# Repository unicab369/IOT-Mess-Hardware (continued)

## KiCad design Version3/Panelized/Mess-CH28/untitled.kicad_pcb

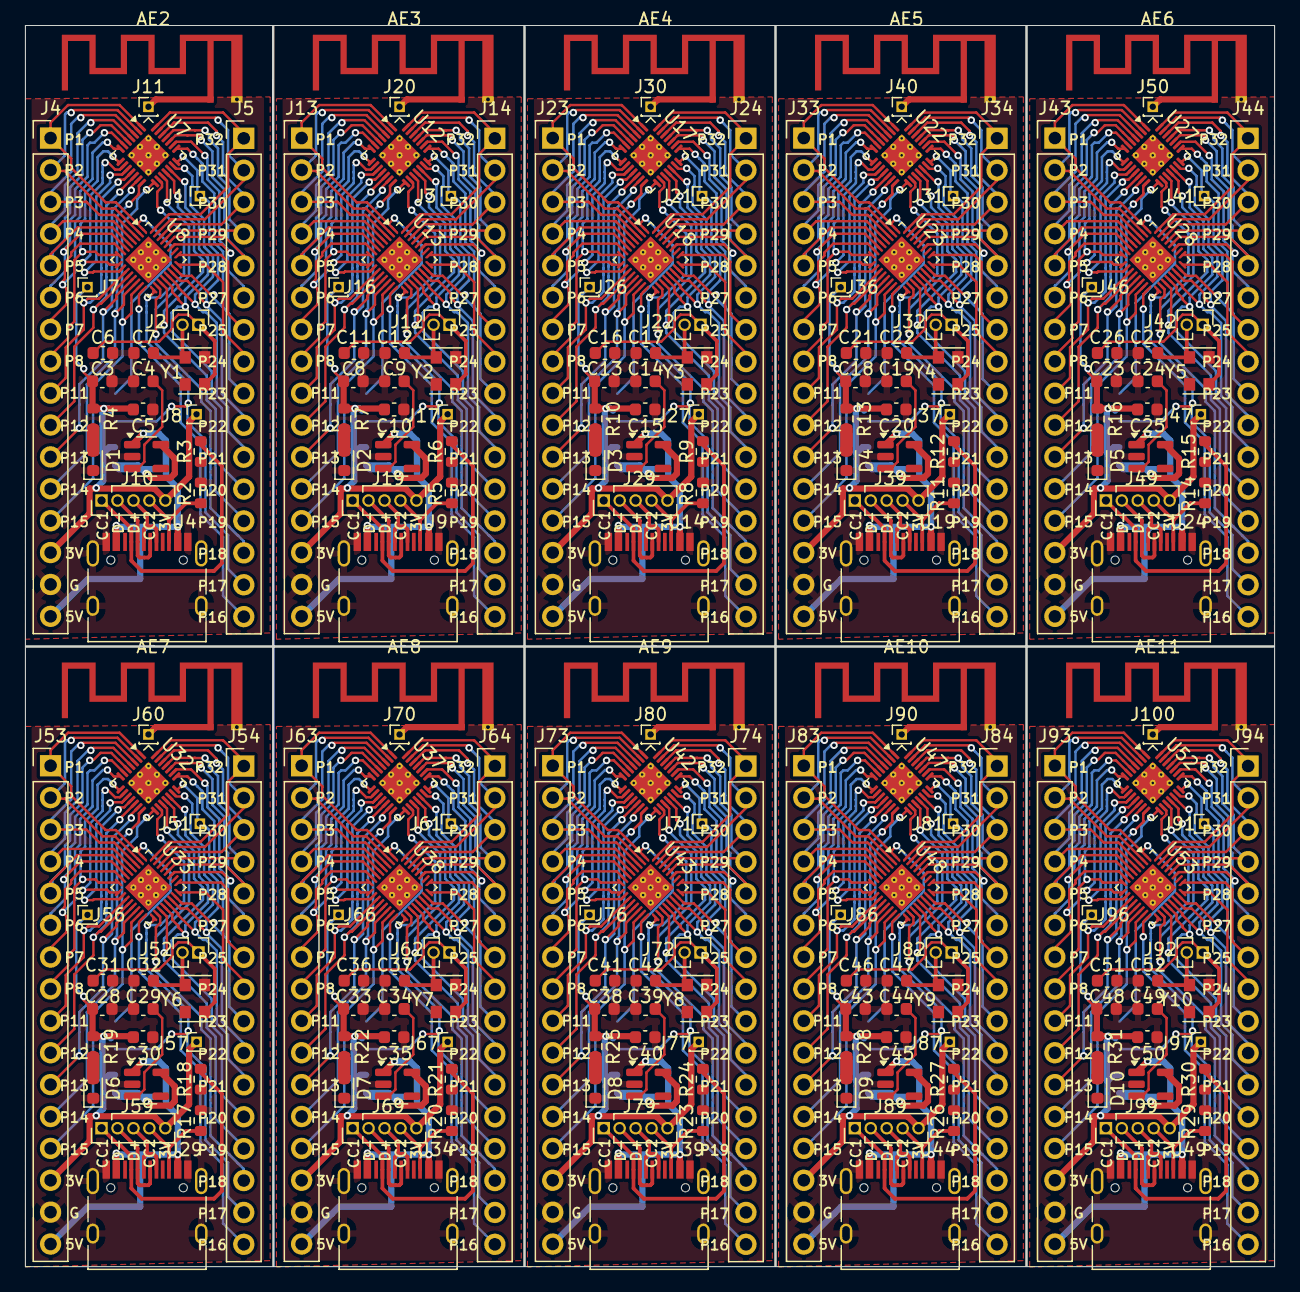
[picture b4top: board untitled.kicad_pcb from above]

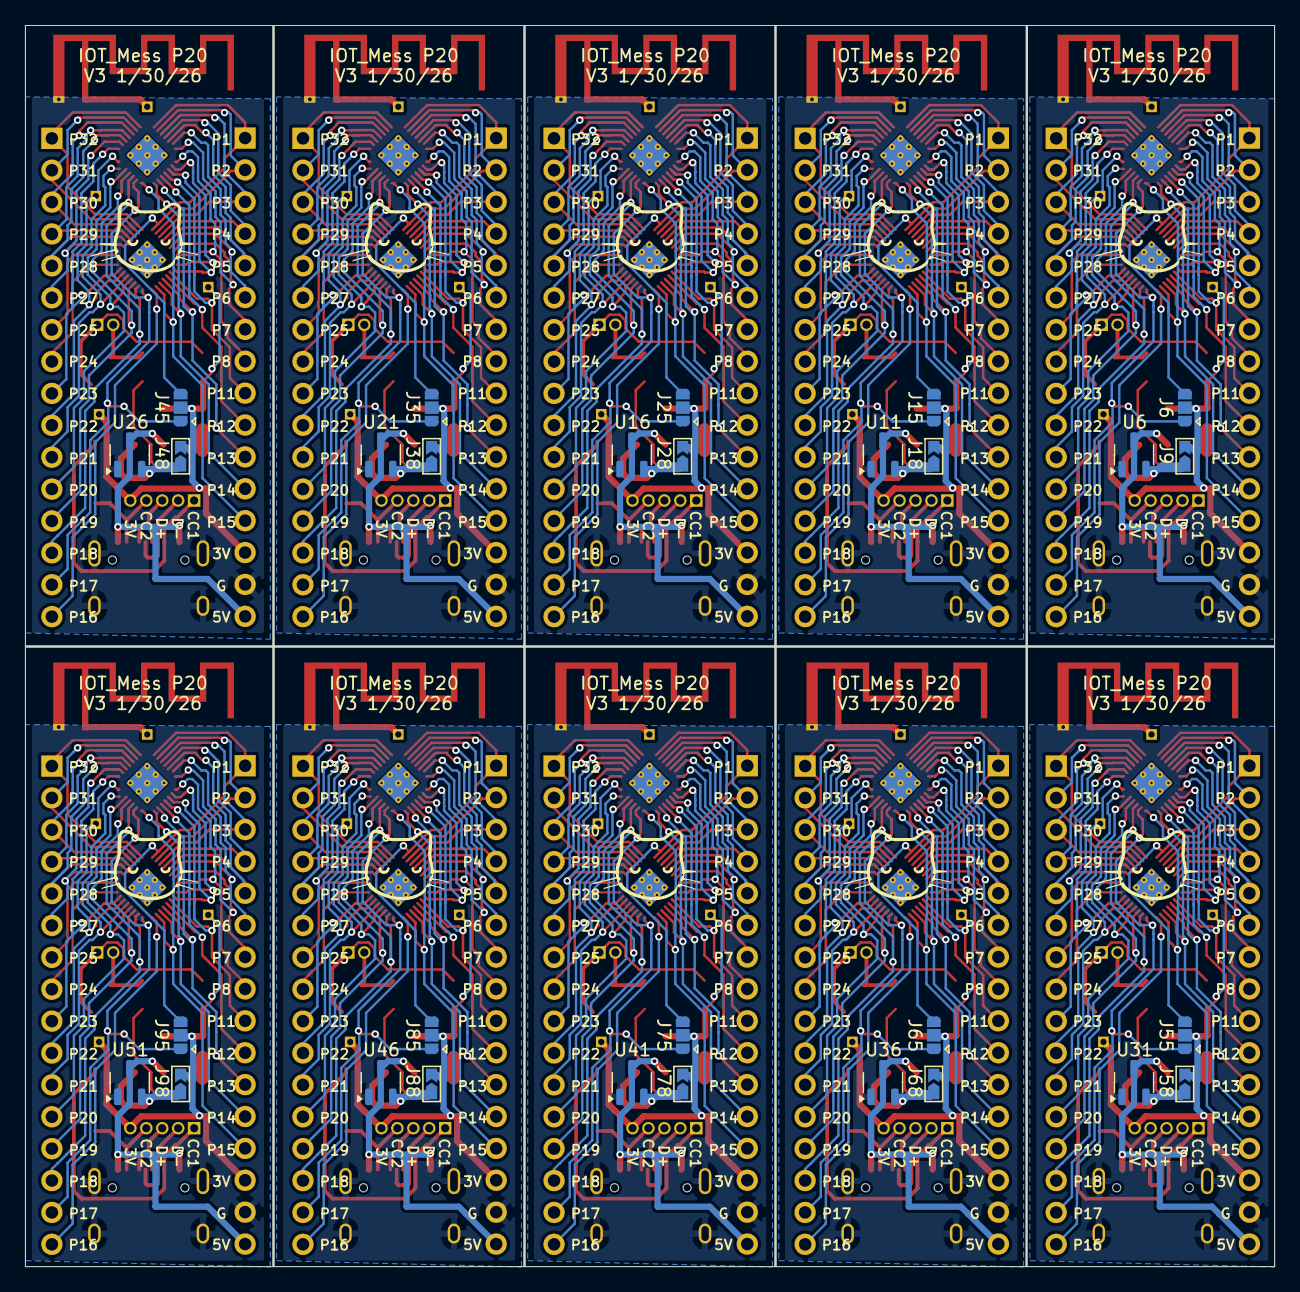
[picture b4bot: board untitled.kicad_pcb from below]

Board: 2 copper layers, 99.5 x 98.9 mm, 260 parts (30 on the bottom side), 45 nets.

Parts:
AE2, AE3, AE4, AE5, AE6, AE7, AE8, AE9, AE10, AE11: Antenna_Shield; Texas_SWRA117D_2.4GHz_Left
C3, C8, C13, C18, C23, C28, C33, C38, C43, C48: 10u; C_0603_1608Metric
C4, C5, C9, C10, C14, C15, C19, C20, C24, C25, C29, C30, C34, C35, C39, C40, C44, C45, C49, C50: 1u; C_0603_1608Metric
C6, C7, C11, C12, C16, C17, C21, C22, C26, C27, C31, C32, C36, C37, C41, C42, C46, C47, C51, C52: 12-25pF; C_0603_1608Metric
D1, D2, D3, D4, D5, D6, D7, D8, D9, D10: LED; LED_0603_1608Metric
J1, J3, J7, J8, J11, J16, J17, J20, J21, J26, J27, J30, J31, J36, J37, J40, J41, J46, J47, J50, J51, J56, J57, J60, J61, J66, J67, J70, J71, J76, J77, J80, J81, J86, J87, J90, J91, J96, J97, J100: Conn_01x01_Pin; PinHeader_1x01_P1.00mm_Vertical
J2, J12, J22, J32, J42, J52, J62, J72, J82, J92: Conn_01x02_Pin; PinHeader_1x02_P1.27mm_Vertical
J4, J5, J13, J14, J23, J24, J33, J34, J43, J44, J53, J54, J63, J64, J73, J74, J83, J84, J93, J94: Conn_01x16_Pin; PinHeader_1x16_P2.54mm_Vertical
J6, J15, J25, J35, J45, J55, J65, J75, J85, J95: Jumper; Jumper-3_P1.3mm_Open_RoundedPad1.0x1.5mm
J9, J18, J28, J38, J48, J58, J68, J78, J88, J98: Jumper_2; Jumpper-triangle
J10, J19, J29, J39, J49, J59, J69, J79, J89, J99: Conn_01x05_Pin; PinHeader_1x05_P1.27mm_Vertical
R2, R3, R5, R6, R8, R9, R11, R12, R14, R15, R17, R18, R20, R21, R23, R24, R26, R27, R29, R30: 5.1K; R_0603_1608Metric
R4, R7, R10, R13, R16, R19, R22, R25, R28, R31: R; R_0603_1608Metric
U4, U9, U14, U19, U24, U29, U34, U39, U44, U49: USB_C_Receptacle_USB2.0_16P; USB_C_Receptacle_HRO_TYPE-C-31-M-12
U5, U10, U15, U20, U25, U30, U35, U40, U45, U50: ME6211C33M5; SOT-23-5
U6, U11, U16, U21, U26, U31, U36, U41, U46, U51: XC6206PxxxMR; SOT-23-3
U7, U12, U17, U22, U27, U32, U37, U42, U47, U52: QFN-28-1EP_4x4mm_P0.4mm_EP2.4x2.4mm_ThermalVias
U8, U13, U18, U23, U28, U33, U38, U43, U48, U53: QFN-32-1EP_4x4mm_P0.4mm_EP2.65x2.65mm_ThermalVias
Y1, Y2, Y3, Y4, Y5, Y6, Y7, Y8, Y9, Y10: XO32; Oscillator_SMD_EuroQuartz_XO32-4Pin_3.2x2.5mm

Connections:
5V: J4.16, J13.16, J23.16, J33.16, J43.16, J53.16, J63.16, J73.16, J83.16, J93.16, U4.A4 (VBUS), U4.A9 (VBUS), U4.B4 (VBUS), U4.B9 (VBUS), U5.1 (V_{IN}), U6.3 (VI), U9.A4 (VBUS), U9.A9 (VBUS), U9.B4 (VBUS), U9.B9 (VBUS), U10.1 (V_{IN}), U11.3 (VI), U14.A4 (VBUS), U14.A9 (VBUS), U14.B4 (VBUS), U14.B9 (VBUS), U15.1 (V_{IN}), U16.3 (VI), U19.A4 (VBUS), U19.A9 (VBUS), U19.B4 (VBUS), U19.B9 (VBUS), U20.1 (V_{IN}), U21.3 (VI), U24.A4 (VBUS), U24.A9 (VBUS), U24.B4 (VBUS), U24.B9 (VBUS), U25.1 (V_{IN}), U26.3 (VI), U29.A4 (VBUS), U29.A9 (VBUS), U29.B4 (VBUS), U29.B9 (VBUS), U30.1 (V_{IN}), U31.3 (VI), U34.A4 (VBUS), U34.A9 (VBUS), U34.B4 (VBUS), U34.B9 (VBUS), U35.1 (V_{IN}), U36.3 (VI), U39.A4 (VBUS), U39.A9 (VBUS), U39.B4 (VBUS), U39.B9 (VBUS), U40.1 (V_{IN}), U41.3 (VI), U44.A4 (VBUS), U44.A9 (VBUS), U44.B4 (VBUS), U44.B9 (VBUS), U45.1 (V_{IN}), U46.3 (VI), U49.A4 (VBUS), U49.A9 (VBUS), U49.B4 (VBUS), U49.B9 (VBUS), U50.1 (V_{IN}), U51.3 (VI)
+3.3V: C3.1, C5.1, C8.1, C10.1, C13.1, C15.1, C18.1, C20.1, C23.1, C25.1, C28.1, C30.1, C33.1, C35.1, C38.1, C40.1, C43.1, C45.1, C48.1, C50.1, J4.14, J6.2 (C), J7.1, J8.1, J9.2 (B), J10.5, J13.14, J15.2 (C), J16.1, J17.1, J18.2 (B), J19.5, J23.14, J25.2 (C), J26.1, J27.1, J28.2 (B), J29.5, J33.14, J35.2 (C), J36.1, J37.1, J38.2 (B), J39.5, J43.14, J45.2 (C), J46.1, J47.1, J48.2 (B), J49.5, J53.14, J55.2 (C), J56.1, J57.1, J58.2 (B), J59.5, J63.14, J65.2 (C), J66.1, J67.1, J68.2 (B), J69.5, J73.14, J75.2 (C), J76.1, J77.1, J78.2 (B), J79.5, J83.14, J85.2 (C), J86.1, J87.1, J88.2 (B), J89.5, J93.14, J95.2 (C), J96.1, J97.1, J98.2 (B), J99.5, R4.1, R7.1, R10.1, R13.1, R16.1, R19.1, R22.1, R25.1, R28.1, R31.1
ANT: AE2.1 (A), AE3.1 (A), AE4.1 (A), AE5.1 (A), AE6.1 (A), AE7.1 (A), AE8.1 (A), AE9.1 (A), AE10.1 (A), AE11.1 (A), J11.1, J20.1, J30.1, J40.1, J50.1, J60.1, J70.1, J80.1, J90.1, J100.1
CC1: J10.1, J19.1, J29.1, J39.1, J49.1, J59.1, J69.1, J79.1, J89.1, J99.1, R3.1, R6.1, R9.1, R12.1, R15.1, R18.1, R21.1, R24.1, R27.1, R30.1, U4.A5 (CC1), U9.A5 (CC1), U14.A5 (CC1), U19.A5 (CC1), U24.A5 (CC1), U29.A5 (CC1), U34.A5 (CC1), U39.A5 (CC1), U44.A5 (CC1), U49.A5 (CC1)
CC2: J10.4, J19.4, J29.4, J39.4, J49.4, J59.4, J69.4, J79.4, J89.4, J99.4, R2.1, R5.1, R8.1, R11.1, R14.1, R17.1, R20.1, R23.1, R26.1, R29.1, U4.B5 (CC2), U9.B5 (CC2), U14.B5 (CC2), U19.B5 (CC2), U24.B5 (CC2), U29.B5 (CC2), U34.B5 (CC2), U39.B5 (CC2), U44.B5 (CC2), U49.B5 (CC2)
D+: J10.3, J19.3, J29.3, J39.3, J49.3, J59.3, J69.3, J79.3, J89.3, J99.3, U4.A6 (D+), U4.B6 (D+), U9.A6 (D+), U9.B6 (D+), U14.A6 (D+), U14.B6 (D+), U19.A6 (D+), U19.B6 (D+), U24.A6 (D+), U24.B6 (D+), U29.A6 (D+), U29.B6 (D+), U34.A6 (D+), U34.B6 (D+), U39.A6 (D+), U39.B6 (D+), U44.A6 (D+), U44.B6 (D+), U49.A6 (D+), U49.B6 (D+)
D-: J10.2, J19.2, J29.2, J39.2, J49.2, J59.2, J69.2, J79.2, J89.2, J99.2, U4.A7 (D-), U4.B7 (D-), U9.A7 (D-), U9.B7 (D-), U14.A7 (D-), U14.B7 (D-), U19.A7 (D-), U19.B7 (D-), U24.A7 (D-), U24.B7 (D-), U29.A7 (D-), U29.B7 (D-), U34.A7 (D-), U34.B7 (D-), U39.A7 (D-), U39.B7 (D-), U44.A7 (D-), U44.B7 (D-), U49.A7 (D-), U49.B7 (D-)
GND: AE2.2 (Shield), AE3.2 (Shield), AE4.2 (Shield), AE5.2 (Shield), AE6.2 (Shield), AE7.2 (Shield), AE8.2 (Shield), AE9.2 (Shield), AE10.2 (Shield), AE11.2 (Shield), C3.2, C4.2, C5.2, C6.2, C7.2, C8.2, C9.2, C10.2, C11.2, C12.2, C13.2, C14.2, C15.2, C16.2, C17.2, C18.2, C19.2, C20.2, C21.2, C22.2, C23.2, C24.2, C25.2, C26.2, C27.2, C28.2, C29.2, C30.2, C31.2, C32.2, C33.2, C34.2, C35.2, C36.2, C37.2, C38.2, C39.2, C40.2, C41.2, C42.2, C43.2, C44.2, C45.2, C46.2, C47.2, C48.2, C49.2, C50.2, C51.2, C52.2, D1.1 (K), D2.1 (K), D3.1 (K), D4.1 (K), D5.1 (K), D6.1 (K), D7.1 (K), D8.1 (K), D9.1 (K), D10.1 (K), J4.15, J13.15, J23.15, J33.15, J43.15, J53.15, J63.15, J73.15, J83.15, J93.15, R2.2, R3.2, R5.2, R6.2, R8.2, R9.2, R11.2, R12.2, R14.2, R15.2, R17.2, R18.2, R20.2, R21.2, R23.2, R24.2, R26.2, R27.2, R29.2, R30.2, U4.A1 (GND), U4.A12 (GND), U4.B1 (GND), U4.B12 (GND), U4.S1 (SHIELD), U5.2 (V_{SS}), U6.1 (GND), U9.A1 (GND), U9.A12 (GND), U9.B1 (GND), U9.B12 (GND), U9.S1 (SHIELD), U10.2 (V_{SS}), U11.1 (GND), U14.A1 (GND), U14.A12 (GND), U14.B1 (GND), U14.B12 (GND), U14.S1 (SHIELD), U15.2 (V_{SS}), U16.1 (GND), U19.A1 (GND), U19.A12 (GND), U19.B1 (GND), U19.B12 (GND), U19.S1 (SHIELD), U20.2 (V_{SS}), U21.1 (GND), U24.A1 (GND), U24.A12 (GND), U24.B1 (GND), U24.B12 (GND), U24.S1 (SHIELD), U25.2 (V_{SS}), U26.1 (GND), U29.A1 (GND), U29.A12 (GND), U29.B1 (GND), U29.B12 (GND), U29.S1 (SHIELD), U30.2 (V_{SS}), U31.1 (GND), U34.A1 (GND), U34.A12 (GND), U34.B1 (GND), U34.B12 (GND), U34.S1 (SHIELD), U35.2 (V_{SS}), U36.1 (GND), U39.A1 (GND), U39.A12 (GND), U39.B1 (GND), U39.B12 (GND), U39.S1 (SHIELD), U40.2 (V_{SS}), U41.1 (GND), U44.A1 (GND), U44.A12 (GND), U44.B1 (GND), U44.B12 (GND), U44.S1 (SHIELD), U45.2 (V_{SS}), U46.1 (GND), U49.A1 (GND), U49.A12 (GND), U49.B1 (GND), U49.B12 (GND), U49.S1 (SHIELD), U50.2 (V_{SS}), U51.1 (GND), Y1.2 (GND), Y1.4 (GND), Y2.2 (GND), Y2.4 (GND), Y3.2 (GND), Y3.4 (GND), Y4.2 (GND), Y4.4 (GND), Y5.2 (GND), Y5.4 (GND), Y6.2 (GND), Y6.4 (GND), Y7.2 (GND), Y7.4 (GND), Y8.2 (GND), Y8.4 (GND), Y9.2 (GND), Y9.4 (GND), Y10.2 (GND), Y10.4 (GND)
LDO_EN: C4.1, C9.1, C14.1, C19.1, C24.1, C29.1, C34.1, C39.1, C44.1, C49.1, U5.3 (CE), U10.3 (CE), U15.3 (CE), U20.3 (CE), U25.3 (CE), U30.3 (CE), U35.3 (CE), U40.3 (CE), U45.3 (CE), U50.3 (CE)
unnamed: D1.2 (A), D2.2 (A), D3.2 (A), D4.2 (A), D5.2 (A), D6.2 (A), D7.2 (A), D8.2 (A), D9.2 (A), D10.2 (A), R4.2, R7.2, R10.2, R13.2, R16.2, R19.2, R22.2, R25.2, R28.2, R31.2
unnamed: C6.1, C11.1, C16.1, C21.1, C26.1, C31.1, C36.1, C41.1, C46.1, C51.1, J2.1, J12.1, J22.1, J32.1, J42.1, J52.1, J62.1, J72.1, J82.1, J92.1, Y1.1 (XI), Y2.1 (XI), Y3.1 (XI), Y4.1 (XI), Y5.1 (XI), Y6.1 (XI), Y7.1 (XI), Y8.1 (XI), Y9.1 (XI), Y10.1 (XI)
unnamed: C7.1, C12.1, C17.1, C22.1, C27.1, C32.1, C37.1, C42.1, C47.1, C52.1, J2.2, J12.2, J22.2, J32.2, J42.2, J52.2, J62.2, J72.2, J82.2, J92.2, Y1.3 (XO), Y2.3 (XO), Y3.3 (XO), Y4.3 (XO), Y5.3 (XO), Y6.3 (XO), Y7.3 (XO), Y8.3 (XO), Y9.3 (XO), Y10.3 (XO)
unnamed: J9.1 (A), J18.1 (A), J28.1 (A), J38.1 (A), J48.1 (A), J58.1 (A), J68.1 (A), J78.1 (A), J88.1 (A), J98.1 (A), U5.5 (V_{OUT}), U6.2 (VO), U10.5 (V_{OUT}), U11.2 (VO), U15.5 (V_{OUT}), U16.2 (VO), U20.5 (V_{OUT}), U21.2 (VO), U25.5 (V_{OUT}), U26.2 (VO), U30.5 (V_{OUT}), U31.2 (VO), U35.5 (V_{OUT}), U36.2 (VO), U40.5 (V_{OUT}), U41.2 (VO), U45.5 (V_{OUT}), U46.2 (VO), U50.5 (V_{OUT}), U51.2 (VO)
P_1: J4.1, J6.3 (B), J13.1, J15.3 (B), J23.1, J25.3 (B), J33.1, J35.3 (B), J43.1, J45.3 (B), J53.1, J55.3 (B), J63.1, J65.3 (B), J73.1, J75.3 (B), J83.1, J85.3 (B), J93.1, J95.3 (B), U7.1 (PB8/BOOT), U8.1 (B3/SWCK-VDD), U12.1 (PB8/BOOT), U13.1 (B3/SWCK-VDD), U17.1 (PB8/BOOT), U18.1 (B3/SWCK-VDD), U22.1 (PB8/BOOT), U23.1 (B3/SWCK-VDD), U27.1 (PB8/BOOT), U28.1 (B3/SWCK-VDD), U32.1 (PB8/BOOT), U33.1 (B3/SWCK-VDD), U37.1 (PB8/BOOT), U38.1 (B3/SWCK-VDD), U42.1 (PB8/BOOT), U43.1 (B3/SWCK-VDD), U47.1 (PB8/BOOT), U48.1 (B3/SWCK-VDD), U52.1 (PB8/BOOT), U53.1 (B3/SWCK-VDD)
P_2: J4.2, J13.2, J23.2, J33.2, J43.2, J53.2, J63.2, J73.2, J83.2, J93.2, U7.2 (PD0/XI-VDD), U8.2 (PA5-VDCID), U12.2 (PD0/XI-VDD), U13.2 (PA5-VDCID), U17.2 (PD0/XI-VDD), U18.2 (PA5-VDCID), U22.2 (PD0/XI-VDD), U23.2 (PA5-VDCID), U27.2 (PD0/XI-VDD), U28.2 (PA5-VDCID), U32.2 (PD0/XI-VDD), U33.2 (PA5-VDCID), U37.2 (PD0/XI-VDD), U38.2 (PA5-VDCID), U42.2 (PD0/XI-VDD), U43.2 (PA5-VDCID), U47.2 (PD0/XI-VDD), U48.2 (PA5-VDCID), U52.2 (PD0/XI-VDD), U53.2 (PA5-VDCID)
P_3: J4.3, J13.3, J23.3, J33.3, J43.3, J53.3, J63.3, J73.3, J83.3, J93.3, U7.3 (PD1/X0), U8.3 (PA6-VSW), U12.3 (PD1/X0), U13.3 (PA6-VSW), U17.3 (PD1/X0), U18.3 (PA6-VSW), U22.3 (PD1/X0), U23.3 (PA6-VSW), U27.3 (PD1/X0), U28.3 (PA6-VSW), U32.3 (PD1/X0), U33.3 (PA6-VSW), U37.3 (PD1/X0), U38.3 (PA6-VSW), U42.3 (PD1/X0), U43.3 (PA6-VSW), U47.3 (PD1/X0), U48.3 (PA6-VSW), U52.3 (PD1/X0), U53.3 (PA6-VSW)
P_4: J4.4, J13.4, J23.4, J33.4, J43.4, J53.4, J63.4, J73.4, J83.4, J93.4, U7.4 (RST-VDDA), U8.4 (PA7/RST-XI-VDCID), U12.4 (RST-VDDA), U13.4 (PA7/RST-XI-VDCID), U17.4 (RST-VDDA), U18.4 (PA7/RST-XI-VDCID), U22.4 (RST-VDDA), U23.4 (PA7/RST-XI-VDCID), U27.4 (RST-VDDA), U28.4 (PA7/RST-XI-VDCID), U32.4 (RST-VDDA), U33.4 (PA7/RST-XI-VDCID), U37.4 (RST-VDDA), U38.4 (PA7/RST-XI-VDCID), U42.4 (RST-VDDA), U43.4 (PA7/RST-XI-VDCID), U47.4 (RST-VDDA), U48.4 (PA7/RST-XI-VDCID), U52.4 (RST-VDDA), U53.4 (PA7/RST-XI-VDCID)
P_5: J4.5, J13.5, J23.5, J33.5, J43.5, J53.5, J63.5, J73.5, J83.5, J93.5, U7.5 (VDDA), U8.5 (PA0-X0-VSW), U12.5 (VDDA), U13.5 (PA0-X0-VSW), U17.5 (VDDA), U18.5 (PA0-X0-VSW), U22.5 (VDDA), U23.5 (PA0-X0-VSW), U27.5 (VDDA), U28.5 (PA0-X0-VSW), U32.5 (VDDA), U33.5 (PA0-X0-VSW), U37.5 (VDDA), U38.5 (PA0-X0-VSW), U42.5 (VDDA), U43.5 (PA0-X0-VSW), U47.5 (VDDA), U48.5 (PA0-X0-VSW), U52.5 (VDDA), U53.5 (PA0-X0-VSW)
P_6: J4.6, J13.6, J23.6, J33.6, J43.6, J53.6, J63.6, J73.6, J83.6, J93.6, U7.6 (PA0/WKUP/A0), U8.6 (PA1/XI), U12.6 (PA0/WKUP/A0), U13.6 (PA1/XI), U17.6 (PA0/WKUP/A0), U18.6 (PA1/XI), U22.6 (PA0/WKUP/A0), U23.6 (PA1/XI), U27.6 (PA0/WKUP/A0), U28.6 (PA1/XI), U32.6 (PA0/WKUP/A0), U33.6 (PA1/XI), U37.6 (PA0/WKUP/A0), U38.6 (PA1/XI), U42.6 (PA0/WKUP/A0), U43.6 (PA1/XI), U47.6 (PA0/WKUP/A0), U48.6 (PA1/XI), U52.6 (PA0/WKUP/A0), U53.6 (PA1/XI)
P_7: J4.7, J13.7, J23.7, J33.7, J43.7, J53.7, J63.7, J73.7, J83.7, J93.7, U7.7 (PA1/A1), U8.7 (PA2/X0), U12.7 (PA1/A1), U13.7 (PA2/X0), U17.7 (PA1/A1), U18.7 (PA2/X0), U22.7 (PA1/A1), U23.7 (PA2/X0), U27.7 (PA1/A1), U28.7 (PA2/X0), U32.7 (PA1/A1), U33.7 (PA2/X0), U37.7 (PA1/A1), U38.7 (PA2/X0), U42.7 (PA1/A1), U43.7 (PA2/X0), U47.7 (PA1/A1), U48.7 (PA2/X0), U52.7 (PA1/A1), U53.7 (PA2/X0)
P_8: J4.8, J13.8, J23.8, J33.8, J43.8, J53.8, J63.8, J73.8, J83.8, J93.8, U7.8 (PA2/A2-CC2), U8.8 (PD0/TX_/SDA_), U12.8 (PA2/A2-CC2), U13.8 (PD0/TX_/SDA_), U17.8 (PA2/A2-CC2), U18.8 (PD0/TX_/SDA_), U22.8 (PA2/A2-CC2), U23.8 (PD0/TX_/SDA_), U27.8 (PA2/A2-CC2), U28.8 (PD0/TX_/SDA_), U32.8 (PA2/A2-CC2), U33.8 (PD0/TX_/SDA_), U37.8 (PA2/A2-CC2), U38.8 (PD0/TX_/SDA_), U42.8 (PA2/A2-CC2), U43.8 (PD0/TX_/SDA_), U47.8 (PA2/A2-CC2), U48.8 (PD0/TX_/SDA_), U52.8 (PA2/A2-CC2), U53.8 (PD0/TX_/SDA_)
P_9: U7.9 (PA3/A3), U8.9 (PA3/RX2_), U12.9 (PA3/A3), U13.9 (PA3/RX2_), U17.9 (PA3/A3), U18.9 (PA3/RX2_), U22.9 (PA3/A3), U23.9 (PA3/RX2_), U27.9 (PA3/A3), U28.9 (PA3/RX2_), U32.9 (PA3/A3), U33.9 (PA3/RX2_), U37.9 (PA3/A3), U38.9 (PA3/RX2_), U42.9 (PA3/A3), U43.9 (PA3/RX2_), U47.9 (PA3/A3), U48.9 (PA3/RX2_), U52.9 (PA3/A3), U53.9 (PA3/RX2_)
P_10: U7.10 (PA4/A4), U8.10 (PB0/NSS), U12.10 (PA4/A4), U13.10 (PB0/NSS), U17.10 (PA4/A4), U18.10 (PB0/NSS), U22.10 (PA4/A4), U23.10 (PB0/NSS), U27.10 (PA4/A4), U28.10 (PB0/NSS), U32.10 (PA4/A4), U33.10 (PB0/NSS), U37.10 (PA4/A4), U38.10 (PB0/NSS), U42.10 (PA4/A4), U43.10 (PB0/NSS), U47.10 (PA4/A4), U48.10 (PB0/NSS), U52.10 (PA4/A4), U53.10 (PB0/NSS)
P_11: J4.9, J13.9, J23.9, J33.9, J43.9, J53.9, J63.9, J73.9, J83.9, J93.9, U7.11 (PA5/A5), U8.11 (PB1/SCK_), U12.11 (PA5/A5), U13.11 (PB1/SCK_), U17.11 (PA5/A5), U18.11 (PB1/SCK_), U22.11 (PA5/A5), U23.11 (PB1/SCK_), U27.11 (PA5/A5), U28.11 (PB1/SCK_), U32.11 (PA5/A5), U33.11 (PB1/SCK_), U37.11 (PA5/A5), U38.11 (PB1/SCK_), U42.11 (PA5/A5), U43.11 (PB1/SCK_), U47.11 (PA5/A5), U48.11 (PB1/SCK_), U52.11 (PA5/A5), U53.11 (PB1/SCK_)
P_12: J4.10, J13.10, J23.10, J33.10, J43.10, J53.10, J63.10, J73.10, J83.10, J93.10, U7.12 (PA6/A6), U8.12 (PB2/MISO_), U12.12 (PA6/A6), U13.12 (PB2/MISO_), U17.12 (PA6/A6), U18.12 (PB2/MISO_), U22.12 (PA6/A6), U23.12 (PB2/MISO_), U27.12 (PA6/A6), U28.12 (PB2/MISO_), U32.12 (PA6/A6), U33.12 (PB2/MISO_), U37.12 (PA6/A6), U38.12 (PB2/MISO_), U42.12 (PA6/A6), U43.12 (PB2/MISO_), U47.12 (PA6/A6), U48.12 (PB2/MISO_), U52.12 (PA6/A6), U53.12 (PB2/MISO_)
P_13: J4.11, J13.11, J23.11, J33.11, J43.11, J53.11, J63.11, J73.11, J83.11, J93.11, U7.13 (PA7/A7-VDD/VIO1), U8.13 (PC0/MOSI_), U12.13 (PA7/A7-VDD/VIO1), U13.13 (PC0/MOSI_), U17.13 (PA7/A7-VDD/VIO1), U18.13 (PC0/MOSI_), U22.13 (PA7/A7-VDD/VIO1), U23.13 (PC0/MOSI_), U27.13 (PA7/A7-VDD/VIO1), U28.13 (PC0/MOSI_), U32.13 (PA7/A7-VDD/VIO1), U33.13 (PC0/MOSI_), U37.13 (PA7/A7-VDD/VIO1), U38.13 (PC0/MOSI_), U42.13 (PA7/A7-VDD/VIO1), U43.13 (PC0/MOSI_), U47.13 (PA7/A7-VDD/VIO1), U48.13 (PC0/MOSI_), U52.13 (PA7/A7-VDD/VIO1), U53.13 (PC0/MOSI_)
P_14: J4.12, J13.12, J23.12, J33.12, J43.12, J53.12, J63.12, J73.12, J83.12, J93.12, U7.14 (PB0/A8-RXP), U8.14 (PC1/SDA/NSS), U12.14 (PB0/A8-RXP), U13.14 (PC1/SDA/NSS), U17.14 (PB0/A8-RXP), U18.14 (PC1/SDA/NSS), U22.14 (PB0/A8-RXP), U23.14 (PC1/SDA/NSS), U27.14 (PB0/A8-RXP), U28.14 (PC1/SDA/NSS), U32.14 (PB0/A8-RXP), U33.14 (PC1/SDA/NSS), U37.14 (PB0/A8-RXP), U38.14 (PC1/SDA/NSS), U42.14 (PB0/A8-RXP), U43.14 (PC1/SDA/NSS), U47.14 (PB0/A8-RXP), U48.14 (PC1/SDA/NSS), U52.14 (PB0/A8-RXP), U53.14 (PC1/SDA/NSS)
P_15: J4.13, J13.13, J23.13, J33.13, J43.13, J53.13, J63.13, J73.13, J83.13, J93.13, U7.15 (PB1/A9-RXN), U8.15 (PC2/SCL), U12.15 (PB1/A9-RXN), U13.15 (PC2/SCL), U17.15 (PB1/A9-RXN), U18.15 (PC2/SCL), U22.15 (PB1/A9-RXN), U23.15 (PC2/SCL), U27.15 (PB1/A9-RXN), U28.15 (PC2/SCL), U32.15 (PB1/A9-RXN), U33.15 (PC2/SCL), U37.15 (PB1/A9-RXN), U38.15 (PC2/SCL), U42.15 (PB1/A9-RXN), U43.15 (PC2/SCL), U47.15 (PB1/A9-RXN), U48.15 (PC2/SCL), U52.15 (PB1/A9-RXN), U53.15 (PC2/SCL)
P_16: J5.16, J14.16, J24.16, J34.16, J44.16, J54.16, J64.16, J74.16, J84.16, J94.16, U8.16 (PC3), U13.16 (PC3), U18.16 (PC3), U23.16 (PC3), U28.16 (PC3), U33.16 (PC3), U38.16 (PC3), U43.16 (PC3), U48.16 (PC3), U53.16 (PC3)
P_17: J5.15, J6.1 (A), J14.15, J15.1 (A), J24.15, J25.1 (A), J34.15, J35.1 (A), J44.15, J45.1 (A), J54.15, J55.1 (A), J64.15, J65.1 (A), J74.15, J75.1 (A), J84.15, J85.1 (A), J94.15, J95.1 (A), U7.16 (GND-TXP), U8.17 (VDD), U12.16 (GND-TXP), U13.17 (VDD), U17.16 (GND-TXP), U18.17 (VDD), U22.16 (GND-TXP), U23.17 (VDD), U27.16 (GND-TXP), U28.17 (VDD), U32.16 (GND-TXP), U33.17 (VDD), U37.16 (GND-TXP), U38.17 (VDD), U42.16 (GND-TXP), U43.17 (VDD), U47.16 (GND-TXP), U48.17 (VDD), U52.16 (GND-TXP), U53.17 (VDD)
P_18: J5.14, J14.14, J24.14, J34.14, J44.14, J54.14, J64.14, J74.14, J84.14, J94.14, U7.17 (VDD-TXN), U8.18 (PC4/A2), U12.17 (VDD-TXN), U13.18 (PC4/A2), U17.17 (VDD-TXN), U18.18 (PC4/A2), U22.17 (VDD-TXN), U23.18 (PC4/A2), U27.17 (VDD-TXN), U28.18 (PC4/A2), U32.17 (VDD-TXN), U33.18 (PC4/A2), U37.17 (VDD-TXN), U38.18 (PC4/A2), U42.17 (VDD-TXN), U43.18 (PC4/A2), U47.17 (VDD-TXN), U48.18 (PC4/A2), U52.17 (VDD-TXN), U53.18 (PC4/A2)
P_19: J5.13, J14.13, J24.13, J34.13, J44.13, J54.13, J64.13, J74.13, J84.13, J94.13, U7.18 (PA9-UDM1), U8.19 (PC5/TX_/SCK), U12.18 (PA9-UDM1), U13.19 (PC5/TX_/SCK), U17.18 (PA9-UDM1), U18.19 (PC5/TX_/SCK), U22.18 (PA9-UDM1), U23.19 (PC5/TX_/SCK), U27.18 (PA9-UDM1), U28.19 (PC5/TX_/SCK), U32.18 (PA9-UDM1), U33.19 (PC5/TX_/SCK), U37.18 (PA9-UDM1), U38.19 (PC5/TX_/SCK), U42.18 (PA9-UDM1), U43.19 (PC5/TX_/SCK), U47.18 (PA9-UDM1), U48.19 (PC5/TX_/SCK), U52.18 (PA9-UDM1), U53.19 (PC5/TX_/SCK)
P_20: J5.12, J14.12, J24.12, J34.12, J44.12, J54.12, J64.12, J74.12, J84.12, J94.12, U7.19 (PA10/PA11/UDM-UDP1), U8.20 (PC6/MOSI), U12.19 (PA10/PA11/UDM-UDP1), U13.20 (PC6/MOSI), U17.19 (PA10/PA11/UDM-UDP1), U18.20 (PC6/MOSI), U22.19 (PA10/PA11/UDM-UDP1), U23.20 (PC6/MOSI), U27.19 (PA10/PA11/UDM-UDP1), U28.20 (PC6/MOSI), U32.19 (PA10/PA11/UDM-UDP1), U33.20 (PC6/MOSI), U37.19 (PA10/PA11/UDM-UDP1), U38.20 (PC6/MOSI), U42.19 (PA10/PA11/UDM-UDP1), U43.20 (PC6/MOSI), U47.19 (PA10/PA11/UDM-UDP1), U48.20 (PC6/MOSI), U52.19 (PA10/PA11/UDM-UDP1), U53.20 (PC6/MOSI)
P_21: J5.11, J14.11, J24.11, J34.11, J44.11, J54.11, J64.11, J74.11, J84.11, J94.11, U7.20 (PA12/UDP-SDIO), U8.21 (PC7/MISO-UDM), U12.20 (PA12/UDP-SDIO), U13.21 (PC7/MISO-UDM), U17.20 (PA12/UDP-SDIO), U18.21 (PC7/MISO-UDM), U22.20 (PA12/UDP-SDIO), U23.21 (PC7/MISO-UDM), U27.20 (PA12/UDP-SDIO), U28.21 (PC7/MISO-UDM), U32.20 (PA12/UDP-SDIO), U33.21 (PC7/MISO-UDM), U37.20 (PA12/UDP-SDIO), U38.21 (PC7/MISO-UDM), U42.20 (PA12/UDP-SDIO), U43.21 (PC7/MISO-UDM), U47.20 (PA12/UDP-SDIO), U48.21 (PC7/MISO-UDM), U52.20 (PA12/UDP-SDIO), U53.21 (PC7/MISO-UDM)
P_22: J1.1, J3.1, J5.10, J14.10, J21.1, J24.10, J31.1, J34.10, J41.1, J44.10, J51.1, J54.10, J61.1, J64.10, J71.1, J74.10, J81.1, J84.10, J91.1, J94.10, U7.21 (PA13/SWIO-VINTA), U8.22 (PB4-UDP), U12.21 (PA13/SWIO-VINTA), U13.22 (PB4-UDP), U17.21 (PA13/SWIO-VINTA), U18.22 (PB4-UDP), U22.21 (PA13/SWIO-VINTA), U23.22 (PB4-UDP), U27.21 (PA13/SWIO-VINTA), U28.22 (PB4-UDP), U32.21 (PA13/SWIO-VINTA), U33.22 (PB4-UDP), U37.21 (PA13/SWIO-VINTA), U38.22 (PB4-UDP), U42.21 (PA13/SWIO-VINTA), U43.22 (PB4-UDP), U47.21 (PA13/SWIO-VINTA), U48.22 (PB4-UDP), U52.21 (PA13/SWIO-VINTA), U53.22 (PB4-UDP)
P_23: J5.9, J14.9, J24.9, J34.9, J44.9, J54.9, J64.9, J74.9, J84.9, J94.9, U7.22 (PA14/SCLK-ANT), U8.23 (PD1/SWIO/SCL_-VINTA), U12.22 (PA14/SCLK-ANT), U13.23 (PD1/SWIO/SCL_-VINTA), U17.22 (PA14/SCLK-ANT), U18.23 (PD1/SWIO/SCL_-VINTA), U22.22 (PA14/SCLK-ANT), U23.23 (PD1/SWIO/SCL_-VINTA), U27.22 (PA14/SCLK-ANT), U28.23 (PD1/SWIO/SCL_-VINTA), U32.22 (PA14/SCLK-ANT), U33.23 (PD1/SWIO/SCL_-VINTA), U37.22 (PA14/SCLK-ANT), U38.23 (PD1/SWIO/SCL_-VINTA), U42.22 (PA14/SCLK-ANT), U43.23 (PD1/SWIO/SCL_-VINTA), U47.22 (PA14/SCLK-ANT), U48.23 (PD1/SWIO/SCL_-VINTA), U52.22 (PA14/SCLK-ANT), U53.23 (PD1/SWIO/SCL_-VINTA)
P_24: J5.8, J14.8, J24.8, J34.8, J44.8, J54.8, J64.8, J74.8, J84.8, J94.8, U8.24 (PD2-SCLK-ANT), U13.24 (PD2-SCLK-ANT), U18.24 (PD2-SCLK-ANT), U23.24 (PD2-SCLK-ANT), U28.24 (PD2-SCLK-ANT), U33.24 (PD2-SCLK-ANT), U38.24 (PD2-SCLK-ANT), U43.24 (PD2-SCLK-ANT), U48.24 (PD2-SCLK-ANT), U53.24 (PD2-SCLK-ANT)
P_25: J5.7, J14.7, J24.7, J34.7, J44.7, J54.7, J64.7, J74.7, J84.7, J94.7, U8.25 (PD3-VDCIA), U13.25 (PD3-VDCIA), U18.25 (PD3-VDCIA), U23.25 (PD3-VDCIA), U28.25 (PD3-VDCIA), U33.25 (PD3-VDCIA), U38.25 (PD3-VDCIA), U43.25 (PD3-VDCIA), U48.25 (PD3-VDCIA), U53.25 (PD3-VDCIA)
P_26: U8.26 (PD4/SDK_), U13.26 (PD4/SDK_), U18.26 (PD4/SDK_), U23.26 (PD4/SDK_), U28.26 (PD4/SDK_), U33.26 (PD4/SDK_), U38.26 (PD4/SDK_), U43.26 (PD4/SDK_), U48.26 (PD4/SDK_), U53.26 (PD4/SDK_)
P_27: J5.6, J14.6, J24.6, J34.6, J44.6, J54.6, J64.6, J74.6, J84.6, J94.6, U7.23 (PA15-SCLK), U8.27 (PD5/MISO_), U12.23 (PA15-SCLK), U13.27 (PD5/MISO_), U17.23 (PA15-SCLK), U18.27 (PD5/MISO_), U22.23 (PA15-SCLK), U23.27 (PD5/MISO_), U27.23 (PA15-SCLK), U28.27 (PD5/MISO_), U32.23 (PA15-SCLK), U33.27 (PD5/MISO_), U37.23 (PA15-SCLK), U38.27 (PD5/MISO_), U42.23 (PA15-SCLK), U43.27 (PD5/MISO_), U47.23 (PA15-SCLK), U48.27 (PD5/MISO_), U52.23 (PA15-SCLK), U53.27 (PD5/MISO_)
P_28: J5.5, J14.5, J24.5, J34.5, J44.5, J54.5, J64.5, J74.5, J84.5, J94.5, U7.24 (PB3-DCK), U8.28 (PD6/MOSI_), U12.24 (PB3-DCK), U13.28 (PD6/MOSI_), U17.24 (PB3-DCK), U18.28 (PD6/MOSI_), U22.24 (PB3-DCK), U23.28 (PD6/MOSI_), U27.24 (PB3-DCK), U28.28 (PD6/MOSI_), U32.24 (PB3-DCK), U33.28 (PD6/MOSI_), U37.24 (PB3-DCK), U38.28 (PD6/MOSI_), U42.24 (PB3-DCK), U43.28 (PD6/MOSI_), U47.24 (PB3-DCK), U48.28 (PD6/MOSI_), U52.24 (PB3-DCK), U53.28 (PD6/MOSI_)
P_29: J5.4, J14.4, J24.4, J34.4, J44.4, J54.4, J64.4, J74.4, J84.4, J94.4, U7.25 (PB4-DIO), U8.29 (PB5/TX_/SCL_), U12.25 (PB4-DIO), U13.29 (PB5/TX_/SCL_), U17.25 (PB4-DIO), U18.29 (PB5/TX_/SCL_), U22.25 (PB4-DIO), U23.29 (PB5/TX_/SCL_), U27.25 (PB4-DIO), U28.29 (PB5/TX_/SCL_), U32.25 (PB4-DIO), U33.29 (PB5/TX_/SCL_), U37.25 (PB4-DIO), U38.29 (PB5/TX_/SCL_), U42.25 (PB4-DIO), U43.29 (PB5/TX_/SCL_), U47.25 (PB4-DIO), U48.29 (PB5/TX_/SCL_), U52.25 (PB4-DIO), U53.29 (PB5/TX_/SCL_)
P_30: J5.3, J14.3, J24.3, J34.3, J44.3, J54.3, J64.3, J74.3, J84.3, J94.3, U7.26 (PB5-UDM), U8.30 (PB6/RX_/SDA_), U12.26 (PB5-UDM), U13.30 (PB6/RX_/SDA_), U17.26 (PB5-UDM), U18.30 (PB6/RX_/SDA_), U22.26 (PB5-UDM), U23.30 (PB6/RX_/SDA_), U27.26 (PB5-UDM), U28.30 (PB6/RX_/SDA_), U32.26 (PB5-UDM), U33.30 (PB6/RX_/SDA_), U37.26 (PB5-UDM), U38.30 (PB6/RX_/SDA_), U42.26 (PB5-UDM), U43.30 (PB6/RX_/SDA_), U47.26 (PB5-UDM), U48.30 (PB6/RX_/SDA_), U52.26 (PB5-UDM), U53.30 (PB6/RX_/SDA_)
P_31: J5.2, J14.2, J24.2, J34.2, J44.2, J54.2, J64.2, J74.2, J84.2, J94.2, U7.27 (PB6-UDP-VIO3), U8.31 (PD7), U12.27 (PB6-UDP-VIO3), U13.31 (PD7), U17.27 (PB6-UDP-VIO3), U18.31 (PD7), U22.27 (PB6-UDP-VIO3), U23.31 (PD7), U27.27 (PB6-UDP-VIO3), U28.31 (PD7), U32.27 (PB6-UDP-VIO3), U33.31 (PD7), U37.27 (PB6-UDP-VIO3), U38.31 (PD7), U42.27 (PB6-UDP-VIO3), U43.31 (PD7), U47.27 (PB6-UDP-VIO3), U48.31 (PD7), U52.27 (PB6-UDP-VIO3), U53.31 (PD7)
P_32: J5.1, J14.1, J24.1, J34.1, J44.1, J54.1, J64.1, J74.1, J84.1, J94.1, U7.28 (PB7-CC1-ANT), U8.32 (PA4/TX2_), U12.28 (PB7-CC1-ANT), U13.32 (PA4/TX2_), U17.28 (PB7-CC1-ANT), U18.32 (PA4/TX2_), U22.28 (PB7-CC1-ANT), U23.32 (PA4/TX2_), U27.28 (PB7-CC1-ANT), U28.32 (PA4/TX2_), U32.28 (PB7-CC1-ANT), U33.32 (PA4/TX2_), U37.28 (PB7-CC1-ANT), U38.32 (PA4/TX2_), U42.28 (PB7-CC1-ANT), U43.32 (PA4/TX2_), U47.28 (PB7-CC1-ANT), U48.32 (PA4/TX2_), U52.28 (PB7-CC1-ANT), U53.32 (PA4/TX2_)
